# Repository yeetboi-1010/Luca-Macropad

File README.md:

<h1>Luca's Macropad</h1>
<p>Hey there! I'm Luca and I made this macropad for a Hackclub project. I added my own little OLED screen, a rotary encoder, some LEDs, and three keyboard switches to make a nice and compact gadget customized for me.</p>
<p>I had tons of fun doing this, and I learned a ton about PCB design and on how to know my way around the command line when I was compiling the firmware. Here's a closer look at what exactly I did:</p>

<h2>KiCad Design</h2>
<p>I used KiCad for the first time to design my PCB.</p>
<p>Here's my schematic:</p>

<p>And my PCB:</p>

<br/>
<h2>Case CAD Design</h2>
<p>Moving onto the case for the project, I used Onshape as my software and cadded the whole case, inserting my KiCad PCB model and some models from GrabCad to help me test fit and show the concept of my idea.</p>
<p>Here's the top of my case:</p>

<p>The bottom:</p>

<p>The fully-assembled case with the PCB:</p>

<p>And my test-fitted parts:</p>

<br/>
<h2>Software</h2>
<p>I used QMK for my software! Was a bit tricky to learn but overall helped me vastly in gaining a better understanding of the command line along with other stuff.</p>
<br/>
<h2>BOM</h2>
<ul>
  <li>Seeed XIAO RP2040 - 1x</li>
  <li>Cherry MX Switches - 3x</li>
  <li>SSD1306 0.91in OLED 4pin 128x32 - 1x</li>
  <li>EC11 Rotary Encoder - 1x</li>
  <li>SK6812 MINI-E LEDs - 2x</li>
  <li>M3x16mm screws - 4x</li>
  <li>M3x5mx4mm heatset inserts - 4x</li>
  <li>QMK Software</li>
  <li>Top + Bottom Case CAD files to be printed</li>
</ul>
<br/>
<h2>Conclusion</h2>
<p>This was super great to make and I can't wait to see what I can use what I've learned in the future! Thanks for reading :)</p>

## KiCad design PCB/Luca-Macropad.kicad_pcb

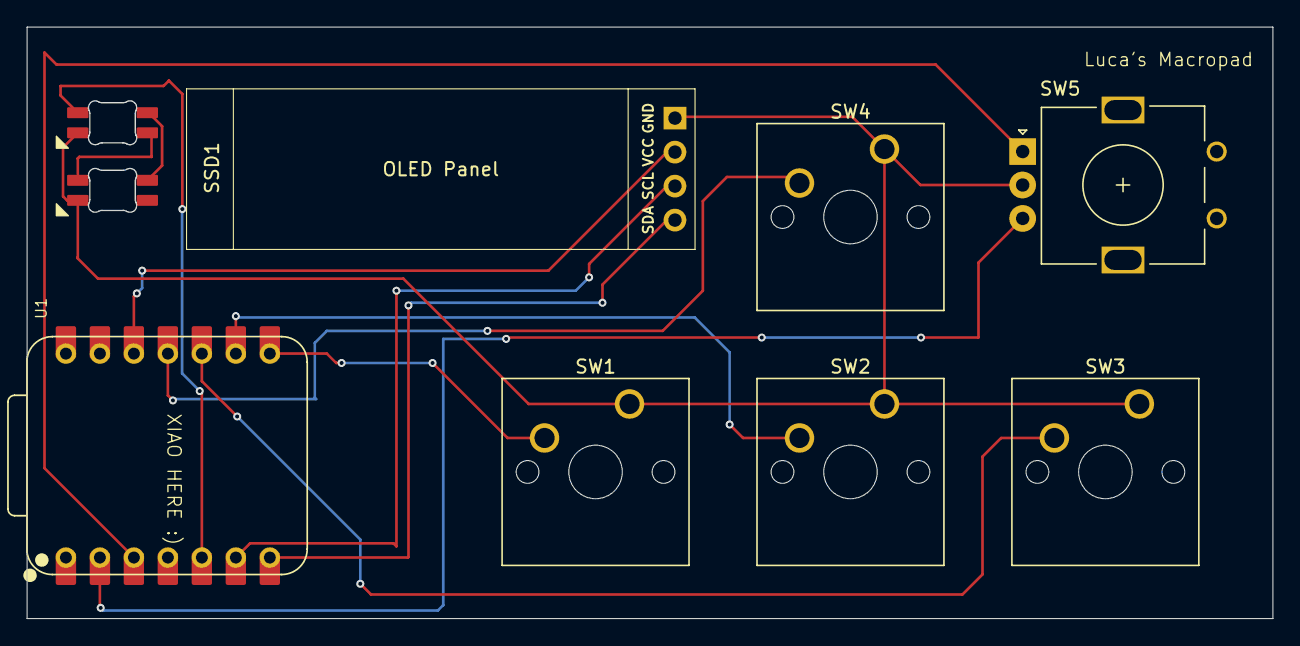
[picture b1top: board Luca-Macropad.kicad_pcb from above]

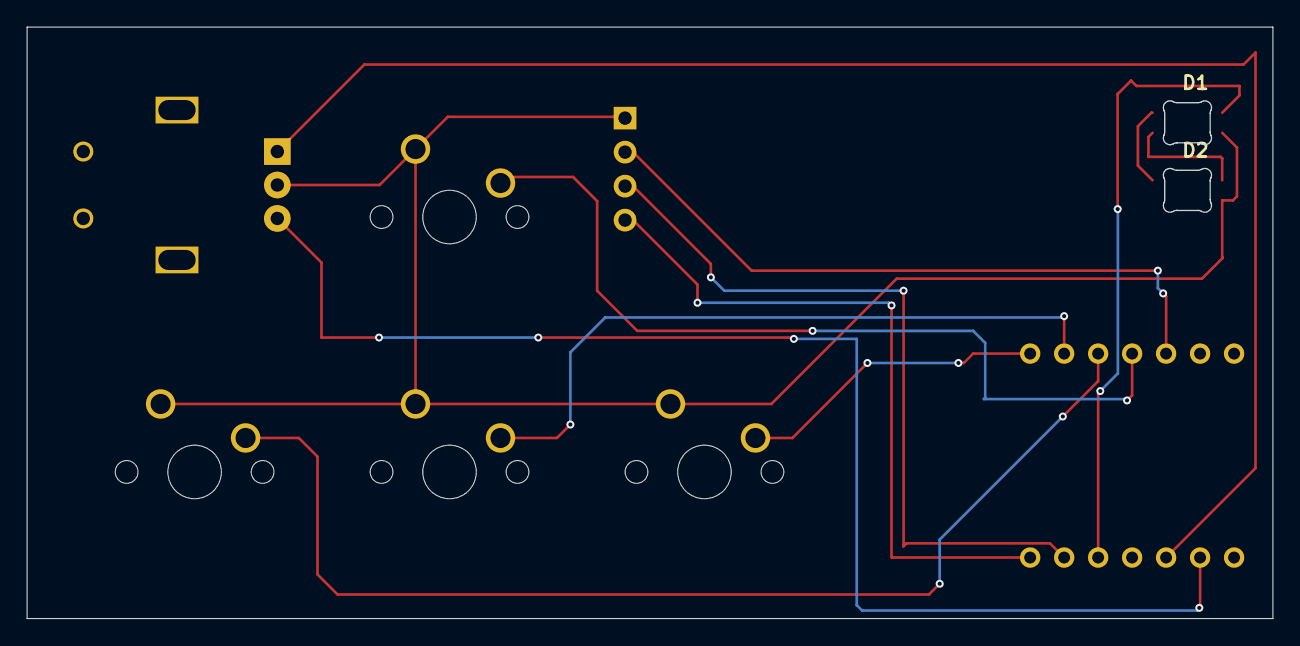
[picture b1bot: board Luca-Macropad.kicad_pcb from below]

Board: 2 copper layers, 93.1 x 44.2 mm, 9 parts (2 on the bottom side), 13 nets.

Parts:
D1, D2: SK6812MINI-E; SK6812MINI-E_fixed
SSD1: SSD1306-0.91-OLED-4pin-128x32
SW1, SW2, SW3, SW4: SW_Push; SW_Cherry_MX_1.00u_PCB
SW5: RotaryEncoder_Switch; RotaryEncoder_Alps_EC11E_Vertical_H20mm
U1: XIAO-RP2040-DIP

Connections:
+5V: D1.1 (VDD), D2.1 (VDD)
GND: D1.3 (VSS), D2.3 (VSS), SSD1.1 (GND), SW1.1, SW2.1, SW3.1, SW4.1, SW5.C
unnamed: D1.4 (DIN), U1.5 (GPIO6/SDA)
unnamed: D1.2 (DOUT), D2.4 (DIN)
unnamed: SSD1.3 (SCL), U1.6 (GPIO7/SCL)
unnamed: SSD1.4 (SDA), U1.7 (GPIO0/TX)
unnamed: SSD1.2 (VCC), U1.12 (3V3)
unnamed: SW1.2, U1.8 (GPIO1/RX)
unnamed: SW2.2, U1.9 (GPIO2/SCK)
unnamed: SW4.2, U1.11 (GPIO3/MOSI)
unnamed: SW3.2, U1.10 (GPIO4/MISO)
unnamed: SW5.B, U1.2 (GPIO27/ADC1/A1)
unnamed: SW5.A, U1.3 (GPIO28/ADC2/A2)

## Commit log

2025-12-18 Added the STEP file and the KiCad files
2025-12-18 Created CAD folder
2025-12-20 Added Project Files
2025-12-20 Create images folder
2025-12-20 Added image files
2025-12-20 removed test file
2025-12-20 Created ReadME!
2025-12-20 fixed small part of ReadME
